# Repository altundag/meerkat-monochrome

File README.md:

# Meerkat Monochrome

Meerkat Monochrome is a monochrome camera project that I started as a hobby. This repository contains the complete design, including PCB layouts, firmware, and supporting tools. The camera hardware consists of:
- an MT9M001C12STM monochrome image sensor
- an RP2354A used as the camera's processing and control unit
- an APS6404L-3SQR QSPI PSRAM for the frame buffer
- an FM25L16B F-RAM to permanently store data (e.g., the frame count)

The image sensor itself is capable of operating at clock speeds up to 48 MHz. However, in this design the pixel clock is set to 6.5 MHz, because the PSRAM frame buffer cannot accept data at higher throughput. This also means the project doesn't require a high-speed PCB, which makes my job easier since I'm not a professional PCB designer.

The PCB design has tiny 0402 components. They require a steady hand, but you can still assemble the board manually using a reflow oven.

The firmware is written entirely in Rust and is actively under development. When this project started, there was no Rust library available to interface with the MT9M001C12STM sensor, so this repository also incleads a tool that automatically generates a library from a JSON sensor description file. Please see the `mt9m001` project for details.

# Examples

An example image taken during prototype PCB testing:

If you have a close look at the image above, you can see the fixed pattern noise. It is more visible when the sensor is evenly exposed to light.

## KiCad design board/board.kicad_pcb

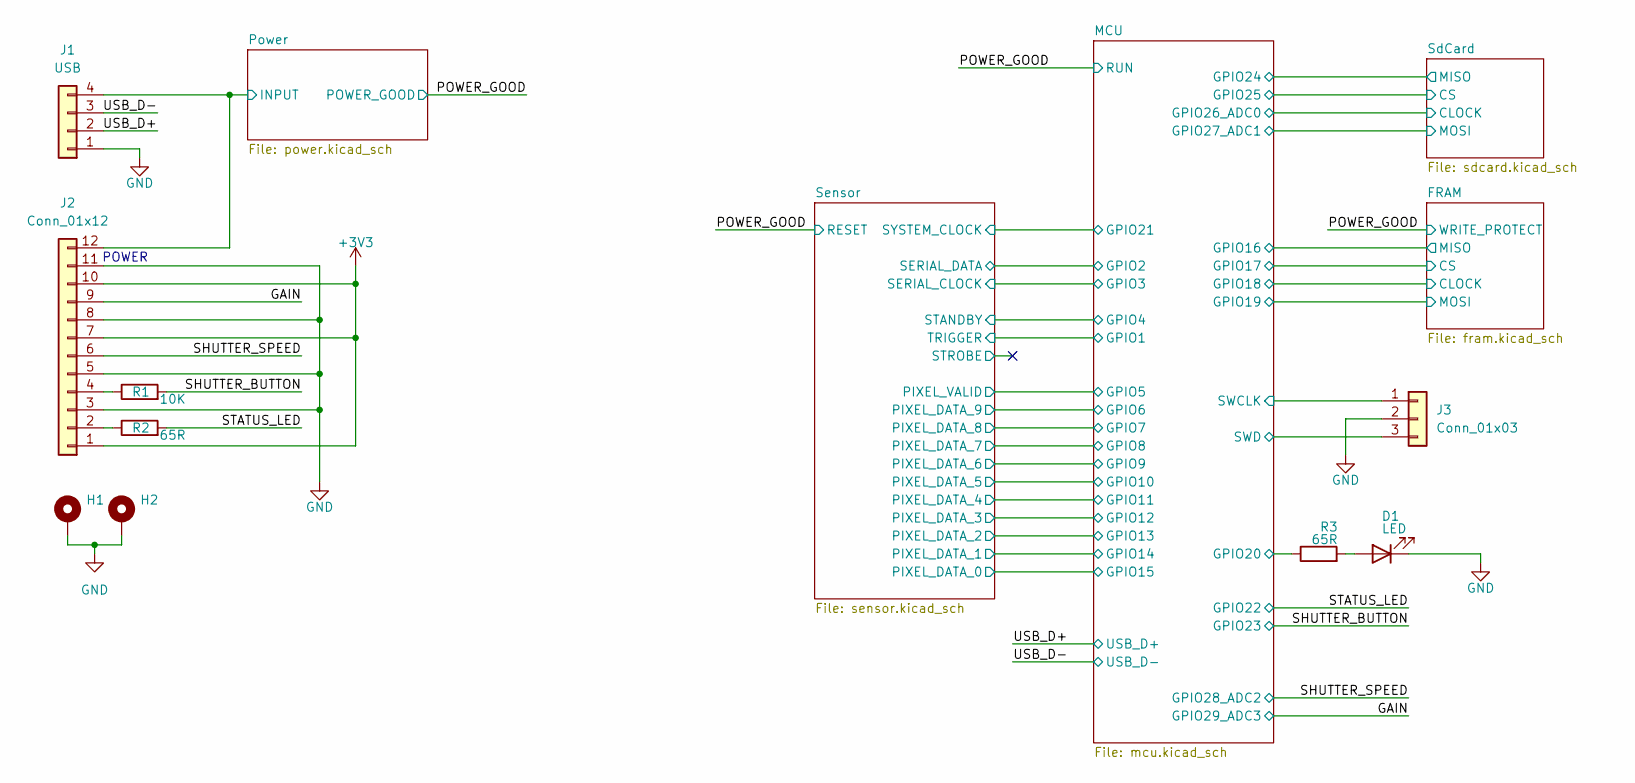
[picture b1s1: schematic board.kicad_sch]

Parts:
D1: LED; LED_0402_1005Metric
H1, H2: MountingHole_Pad; MountingHole_2.2mm_M2_Pad_Via
J1: USB; PinHeader_1x04_P1.27mm_Vertical
J2: Conn_01x12; Hirose_DF52-12S-0.8H_1x12-1MP_P0.80mm_Horizontal
J3: Conn_01x03; PinHeader_1x03_P1.00mm_Vertical
R1: 10K; R_0402_1005Metric
R2, R3: 65R; R_0402_1005Metric

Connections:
+3V3: J2.1, J2.7, J2.10; also elsewhere on the board
/GAIN: J2.9; also elsewhere on the board
/MCU/GPIO20: R3.1; also elsewhere on the board
/MCU/SWCLK: J3.1; also elsewhere on the board
/MCU/SWD: J3.3; also elsewhere on the board
/Power/INPUT: J1.4, J2.12; also elsewhere on the board
/SHUTTER_BUTTON: R1.2; also elsewhere on the board
/SHUTTER_SPEED: J2.6; also elsewhere on the board
/STATUS_LED: R2.2; also elsewhere on the board
/USB_D+: J1.2; also elsewhere on the board
/USB_D-: J1.3; also elsewhere on the board
GND: D1.1 (K), H1.1, H2.1, J1.1, J2.3, J2.5, J2.8, J2.11, J3.2; also elsewhere on the board
unnamed: D1.2 (A), R3.2
unnamed: J2.2, R2.1
unnamed: J2.4, R1.1

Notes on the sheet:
POWER

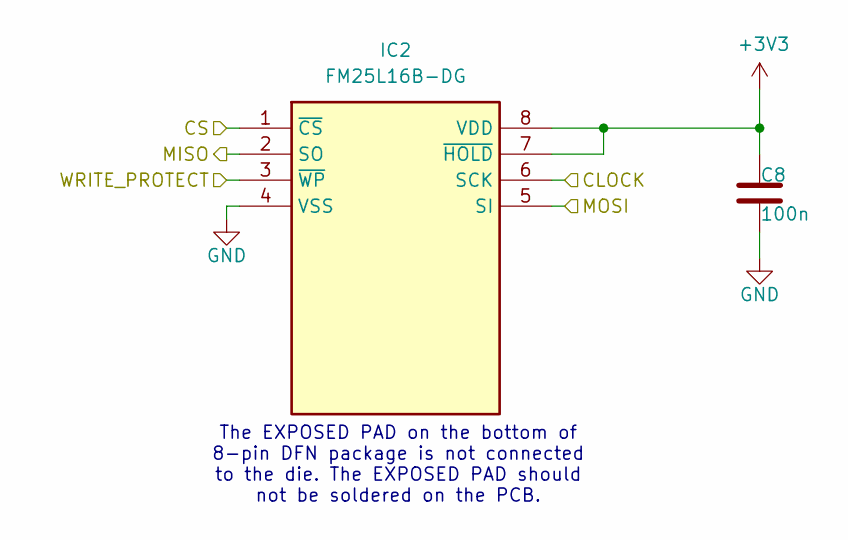
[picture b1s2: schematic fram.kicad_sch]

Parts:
C8: 100n; C_0402_1005Metric
IC2: FM25L16B-DG; Mouser Part Number 877-FM25L16B-DG

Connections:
+3V3: C8.2, IC2.7 (~HOLD), IC2.8 (VDD); also elsewhere on the board
/FRAM/CLOCK: IC2.6 (SCK); also elsewhere on the board
/FRAM/CS: IC2.1 (~CS); also elsewhere on the board
/FRAM/MISO: IC2.2 (SO); also elsewhere on the board
/FRAM/MOSI: IC2.5 (SI); also elsewhere on the board
/POWER_GOOD: IC2.3 (~WP); also elsewhere on the board
GND: C8.1, IC2.4 (VSS); also elsewhere on the board

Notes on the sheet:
The EXPOSED PAD on the bottom of 8-pin DFN package is not connected to the die. The EXPOSED PAD should not be soldered on the PCB.

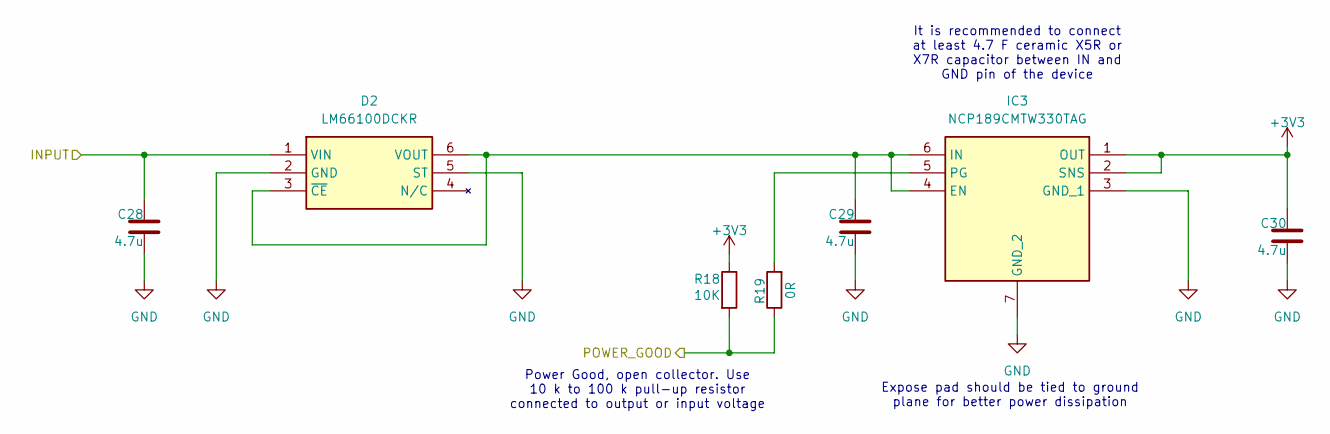
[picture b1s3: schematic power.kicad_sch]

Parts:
C28, C29, C30: 4.7u; C_0402_1005Metric
D2: LM66100DCKR; Mouser Part Number 595-LM66100DCKR
IC3: NCP189CMTW330TAG; Mouser Part Number 863-NCP189CMTW330TAG
R18: 10K; R_0402_1005Metric
R19: 0R; R_0402_1005Metric_small_pads

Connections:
+3V3: C30.2, IC3.1 (OUT), IC3.2 (SNS), R18.1; also elsewhere on the board
/POWER_GOOD: R18.2, R19.1; also elsewhere on the board
/Power/INPUT: C28.2, D2.1 (VIN); also elsewhere on the board
GND: C28.1, C29.1, C30.1, D2.2 (GND), D2.5 (ST), IC3.3 (GND_1), IC3.7 (GND_2); also elsewhere on the board
unnamed: C29.2, D2.3 (~CE), D2.6 (VOUT), IC3.4 (EN), IC3.6 (IN)
unnamed: IC3.5 (PG), R19.2

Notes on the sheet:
Power Good, open collector. Use 10 k to 100 k pull−up resistor connected to output or input voltage
It is recommended to connect at least 4.7 F ceramic X5R or X7R capacitor between IN and GND pin of the device
Expose pad should be tied to ground plane for better power dissipation

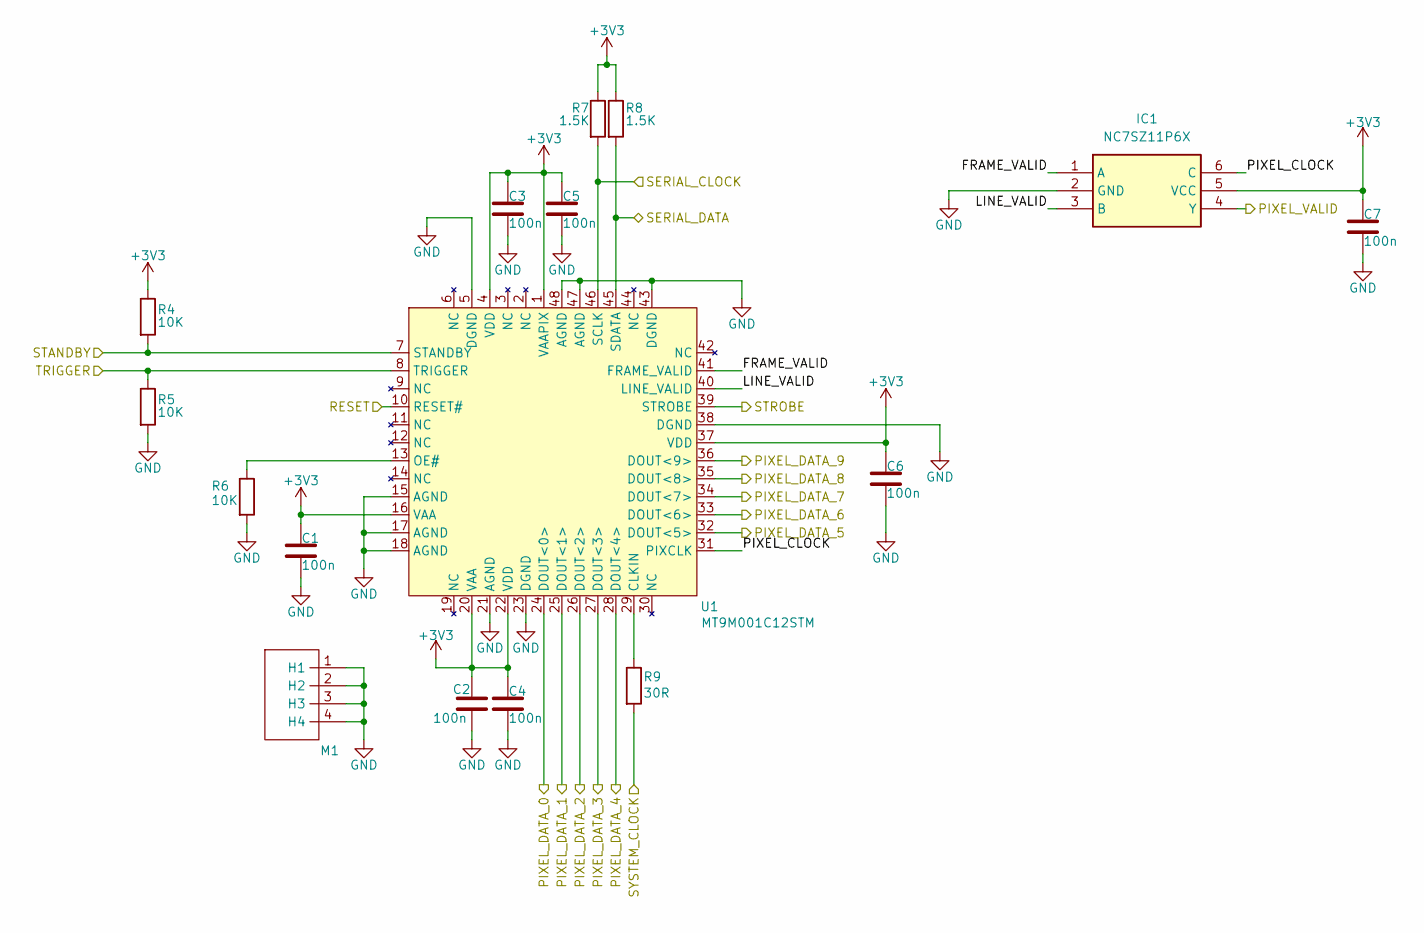
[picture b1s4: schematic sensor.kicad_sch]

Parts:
C1, C2, C3, C4, C5, C6, C7: 100n; C_0402_1005Metric
IC1: NC7SZ11P6X; Mouser Part Number 512-NC7SZ11P6X
M1: c-mount-03
R4, R5, R6: 10K; R_0402_1005Metric
R7, R8: 1.5K; R_0402_1005Metric
R9: 30R; R_0402_1005Metric
U1: MT9M001C12STM

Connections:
+3V3: C1.2, C2.2, C3.2, C4.2, C5.2, C6.2, C7.2, IC1.5 (VCC), R4.1, R7.1, R8.1, U1.1 (VAAPIX), U1.4 (VDD), U1.16 (VAA), U1.20 (VAA), U1.22 (VDD), U1.37 (VDD); also elsewhere on the board
/MCU/GPIO1: R5.1, U1.8 (TRIGGER); also elsewhere on the board
/MCU/GPIO2: R8.2, U1.45 (SDATA); also elsewhere on the board
/MCU/GPIO3: R7.2, U1.46 (SCLK); also elsewhere on the board
/MCU/GPIO4: R4.2, U1.7 (STANDBY); also elsewhere on the board
/MCU/GPIO5: IC1.4 (Y); also elsewhere on the board
/MCU/GPIO6: U1.36 (DOUT<9>); also elsewhere on the board
/MCU/GPIO7: U1.35 (DOUT<8>); also elsewhere on the board
/MCU/GPIO8: U1.34 (DOUT<7>); also elsewhere on the board
/MCU/GPIO9: U1.33 (DOUT<6>); also elsewhere on the board
/MCU/GPIO10: U1.32 (DOUT<5>); also elsewhere on the board
/MCU/GPIO11: U1.28 (DOUT<4>); also elsewhere on the board
/MCU/GPIO12: U1.27 (DOUT<3>); also elsewhere on the board
/MCU/GPIO13: U1.26 (DOUT<2>); also elsewhere on the board
/MCU/GPIO14: U1.25 (DOUT<1>); also elsewhere on the board
/MCU/GPIO15: U1.24 (DOUT<0>); also elsewhere on the board
/MCU/GPIO21: R9.2; also elsewhere on the board
/POWER_GOOD: U1.10 (RESET#); also elsewhere on the board
/Sensor/FRAME_VALID: IC1.1 (A), U1.41 (FRAME_VALID)
/Sensor/LINE_VALID: IC1.3 (B), U1.40 (LINE_VALID)
/Sensor/PIXEL_CLOCK: IC1.6 (C), U1.31 (PIXCLK)
/Sensor/STROBE: U1.39 (STROBE)
GND: C1.1, C2.1, C3.1, C4.1, C5.1, C6.1, C7.1, IC1.2 (GND), M1.1 (H1), M1.2 (H2), M1.3 (H3), M1.4 (H4), R5.2, R6.2, U1.5 (DGND), U1.15 (AGND), U1.17 (AGND), U1.18 (AGND), U1.21 (AGND), U1.23 (DGND), U1.38 (DGND), U1.43 (DGND), U1.47 (AGND), U1.48 (AGND); also elsewhere on the board
unnamed: R9.1, U1.29 (CLKIN)
unnamed: R6.1, U1.13 (OE#)

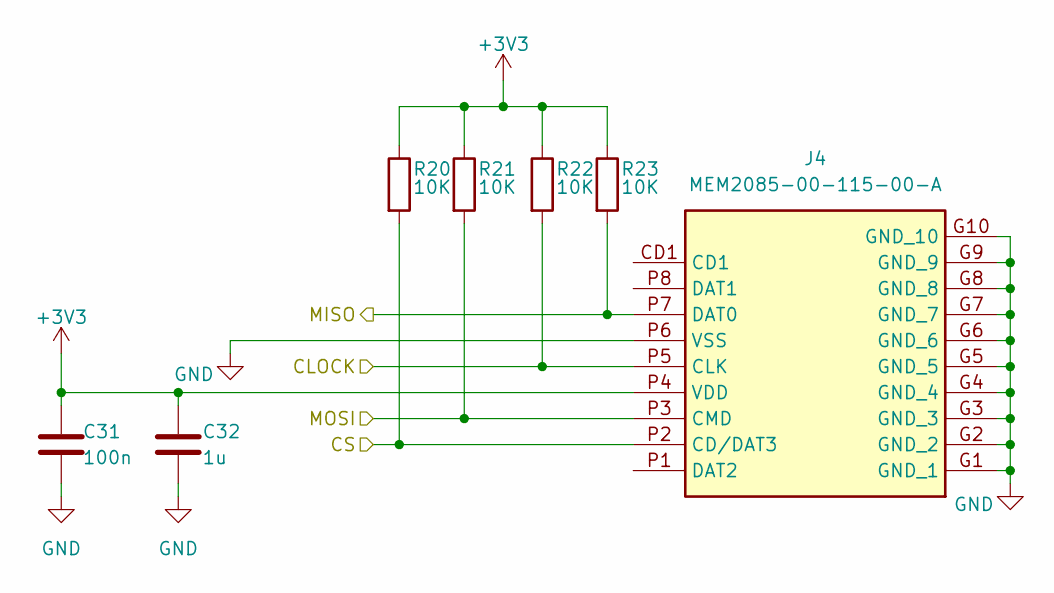
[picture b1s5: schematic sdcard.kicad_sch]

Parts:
C31: 100n; C_0402_1005Metric
C32: 1u; C_0402_1005Metric
J4: MEM2085-00-115-00-A; MEM20850011500A; Mouser Part Number 640-MEM20850011500A
R20, R21, R22, R23: 10K; R_0402_1005Metric_small_pads

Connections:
+3V3: C31.2, C32.2, J4.P4 (VDD), R20.1, R21.1, R22.1, R23.1; also elsewhere on the board
/MCU/GPIO24: J4.P7 (DAT0), R23.2; also elsewhere on the board
/MCU/GPIO25: J4.P2 (CD/DAT3), R20.2; also elsewhere on the board
/MCU/GPIO26_ADC0: J4.P5 (CLK), R22.2; also elsewhere on the board
/MCU/GPIO27_ADC1: J4.P3 (CMD), R21.2; also elsewhere on the board
GND: C31.1, C32.1, J4.G1 (GND_1), J4.G2 (GND_2), J4.G3 (GND_3), J4.G4 (GND_4), J4.G5 (GND_5), J4.G6 (GND_6), J4.G7 (GND_7), J4.G8 (GND_8), J4.G9 (GND_9), J4.G10 (GND_10), J4.P6 (VSS); also elsewhere on the board

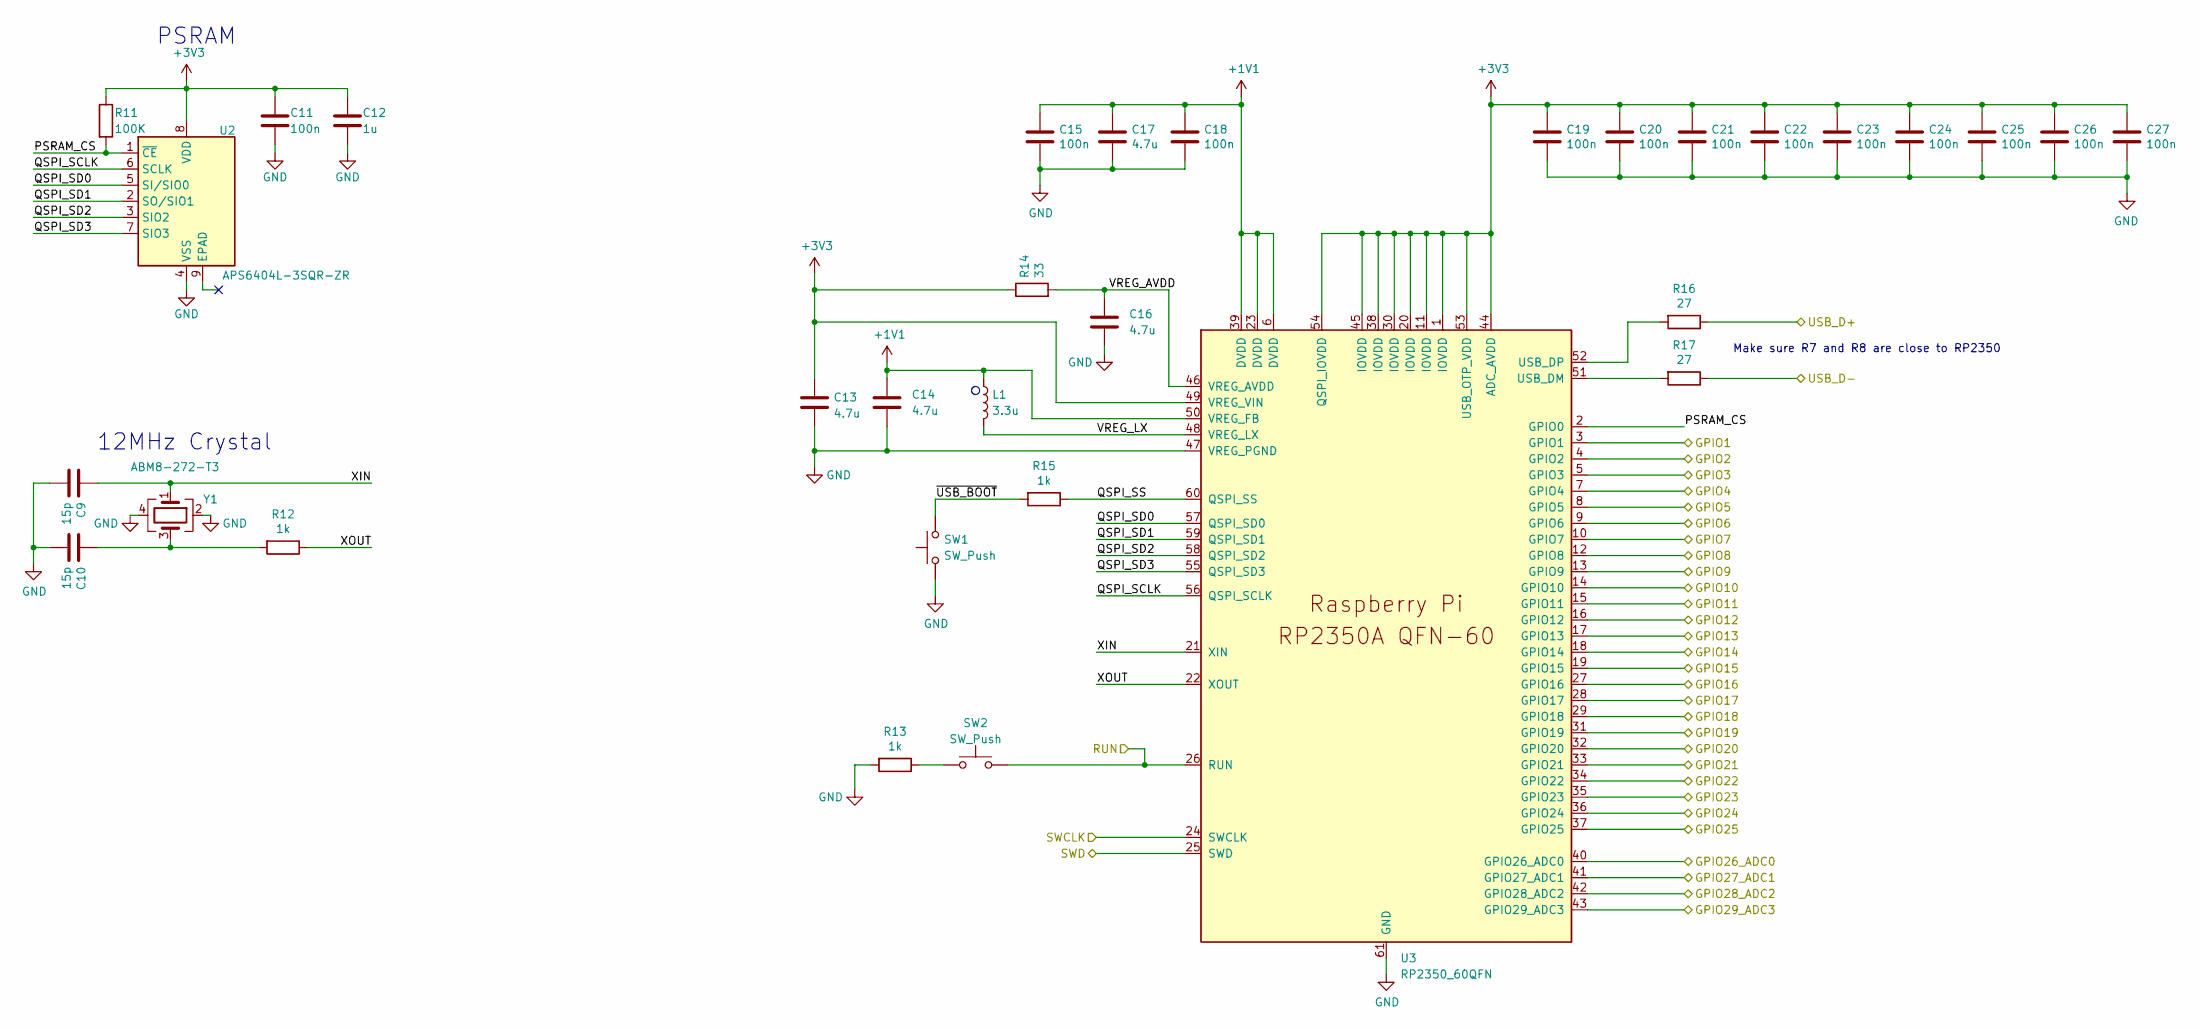
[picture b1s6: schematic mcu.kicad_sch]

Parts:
C9, C10: 15p; C_0402_1005Metric
C11, C15, C18, C19, C20, C21, C22, C23, C24, C25, C26, C27: 100n; C_0402_1005Metric
C12: 1u; C_0402_1005Metric
C13, C14: 4.7u; C_0402_1005Metric_small_pads
C16, C17: 4.7u; C_0402_1005Metric
L1: 3.3u; AOTA-B201610S3R3-101-T
R11: 100K; R_0402_1005Metric_small_pads
R12, R13: 1k; R_0402_1005Metric
R14: 33; R_0402_1005Metric
R15: 1k; R_0402_1005Metric_small_pads
R16, R17: 27; R_0402_1005Metric
SW1, SW2: SW_Push; SW_SPST_B3U-1000P
U2: APS6404L-3SQR-ZR; Winbond_USON-8-1EP_3x2mm_P0.5mm_EP0.2x1.6mm
U3: RP2350_60QFN; RP2350-QFN-60-1EP_7x7_P0.4mm_EP3.4x3.4mm_ThermalVias
Y1: ABM8-272-T3; ABM8272T3

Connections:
+1V1: C14.1, C15.1, C17.1, C18.1, L1.1, U3.6 (DVDD), U3.23 (DVDD), U3.39 (DVDD), U3.50 (VREG_FB)
+3V3: C11.2, C12.2, C13.1, C19.1, C20.1, C21.1, C22.1, C23.1, C24.1, C25.1, C26.1, C27.1, R11.1, R14.1, U2.8 (VDD), U3.1 (IOVDD), U3.11 (IOVDD), U3.20 (IOVDD), U3.30 (IOVDD), U3.38 (IOVDD), U3.44 (ADC_AVDD), U3.45 (IOVDD), U3.49 (VREG_VIN), U3.53 (USB_OTP_VDD), U3.54 (QSPI_IOVDD); also elsewhere on the board
/FRAM/CLOCK: U3.29 (GPIO18); also elsewhere on the board
/FRAM/CS: U3.28 (GPIO17); also elsewhere on the board
/FRAM/MISO: U3.27 (GPIO16); also elsewhere on the board
/FRAM/MOSI: U3.31 (GPIO19); also elsewhere on the board
/GAIN: U3.43 (GPIO29_ADC3); also elsewhere on the board
/MCU/GPIO1: U3.3 (GPIO1); also elsewhere on the board
/MCU/GPIO2: U3.4 (GPIO2); also elsewhere on the board
/MCU/GPIO3: U3.5 (GPIO3); also elsewhere on the board
/MCU/GPIO4: U3.7 (GPIO4); also elsewhere on the board
/MCU/GPIO5: U3.8 (GPIO5); also elsewhere on the board
/MCU/GPIO6: U3.9 (GPIO6); also elsewhere on the board
/MCU/GPIO7: U3.10 (GPIO7); also elsewhere on the board
/MCU/GPIO8: U3.12 (GPIO8); also elsewhere on the board
/MCU/GPIO9: U3.13 (GPIO9); also elsewhere on the board
/MCU/GPIO10: U3.14 (GPIO10); also elsewhere on the board
/MCU/GPIO11: U3.15 (GPIO11); also elsewhere on the board
/MCU/GPIO12: U3.16 (GPIO12); also elsewhere on the board
/MCU/GPIO13: U3.17 (GPIO13); also elsewhere on the board
/MCU/GPIO14: U3.18 (GPIO14); also elsewhere on the board
/MCU/GPIO15: U3.19 (GPIO15); also elsewhere on the board
/MCU/GPIO20: U3.32 (GPIO20); also elsewhere on the board
/MCU/GPIO21: U3.33 (GPIO21); also elsewhere on the board
/MCU/GPIO24: U3.36 (GPIO24); also elsewhere on the board
/MCU/GPIO25: U3.37 (GPIO25); also elsewhere on the board
/MCU/GPIO26_ADC0: U3.40 (GPIO26_ADC0); also elsewhere on the board
/MCU/GPIO27_ADC1: U3.41 (GPIO27_ADC1); also elsewhere on the board
/MCU/PSRAM_CS: R11.2, U2.1 (~CE), U3.2 (GPIO0)
/MCU/QSPI_SCLK: U2.6 (SCLK), U3.56 (QSPI_SCLK)
/MCU/QSPI_SD0: U2.5 (SI/SIO0), U3.57 (QSPI_SD0)
/MCU/QSPI_SD1: U2.2 (SO/SIO1), U3.59 (QSPI_SD1)
/MCU/QSPI_SD2: U2.3 (SIO2), U3.58 (QSPI_SD2)
/MCU/QSPI_SD3: U2.7 (SIO3), U3.55 (QSPI_SD3)
/MCU/QSPI_SS: R15.1, U3.60 (QSPI_SS)
/MCU/SWCLK: U3.24 (SWCLK); also elsewhere on the board
/MCU/SWD: U3.25 (SWD); also elsewhere on the board
/MCU/VREG_AVDD: C16.1, R14.2, U3.46 (VREG_AVDD)
/MCU/VREG_LX: L1.2, U3.48 (VREG_LX)
/MCU/XIN: C9.1, U3.21 (XIN), Y1.1
/MCU/XOUT: R12.1, U3.22 (XOUT)
/MCU/~USB_BOOT: R15.2, SW1.2
/POWER_GOOD: SW2.2, U3.26 (RUN); also elsewhere on the board
/SHUTTER_BUTTON: U3.35 (GPIO23); also elsewhere on the board
/SHUTTER_SPEED: U3.42 (GPIO28_ADC2); also elsewhere on the board
/STATUS_LED: U3.34 (GPIO22); also elsewhere on the board
/USB_D+: R16.1; also elsewhere on the board
/USB_D-: R17.1; also elsewhere on the board
GND: C9.2, C10.2, C11.1, C12.1, C13.2, C14.2, C15.2, C16.2, C17.2, C18.2, C19.2, C20.2, C21.2, C22.2, C23.2, C24.2, C25.2, C26.2, C27.2, R13.2, SW1.1, U2.4 (VSS), U3.47 (VREG_PGND), U3.61 (GND), Y1.2, Y1.4; also elsewhere on the board
unnamed: C10.1, R12.2, Y1.3
unnamed: R13.1, SW2.1
unnamed: R17.2, U3.51 (USB_DM)
unnamed: R16.2, U3.52 (USB_DP)

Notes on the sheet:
Make sure R7 and R8 are close to RP2350
PSRAM
12MHz Crystal

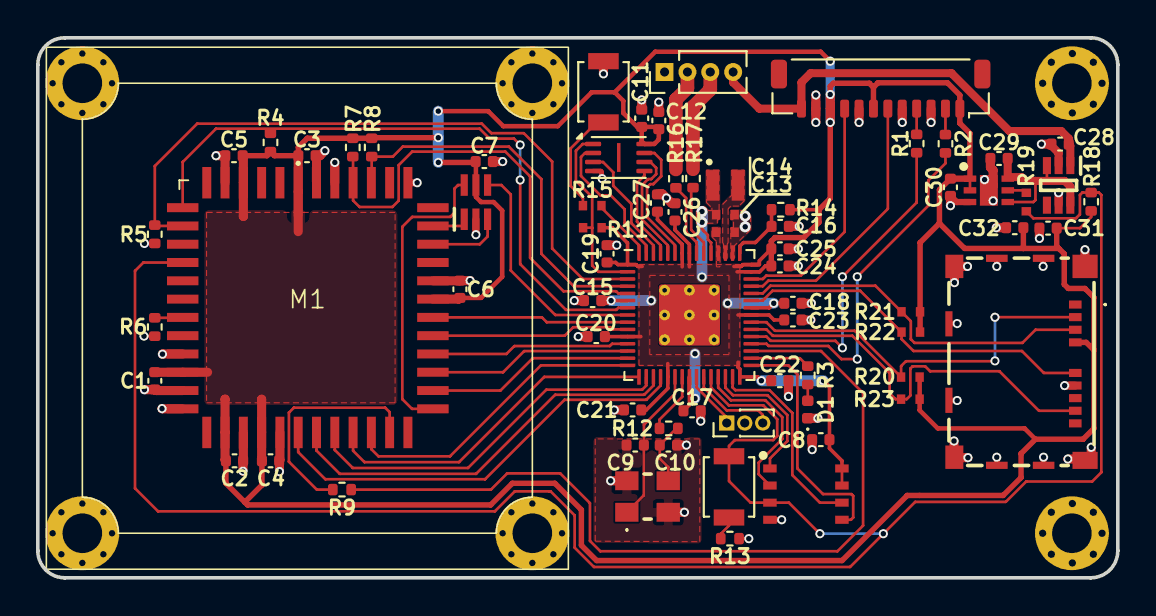
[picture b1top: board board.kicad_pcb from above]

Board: 2 copper layers, 60.0 x 30.0 mm, 73 parts (0 on the bottom side), 64 nets.

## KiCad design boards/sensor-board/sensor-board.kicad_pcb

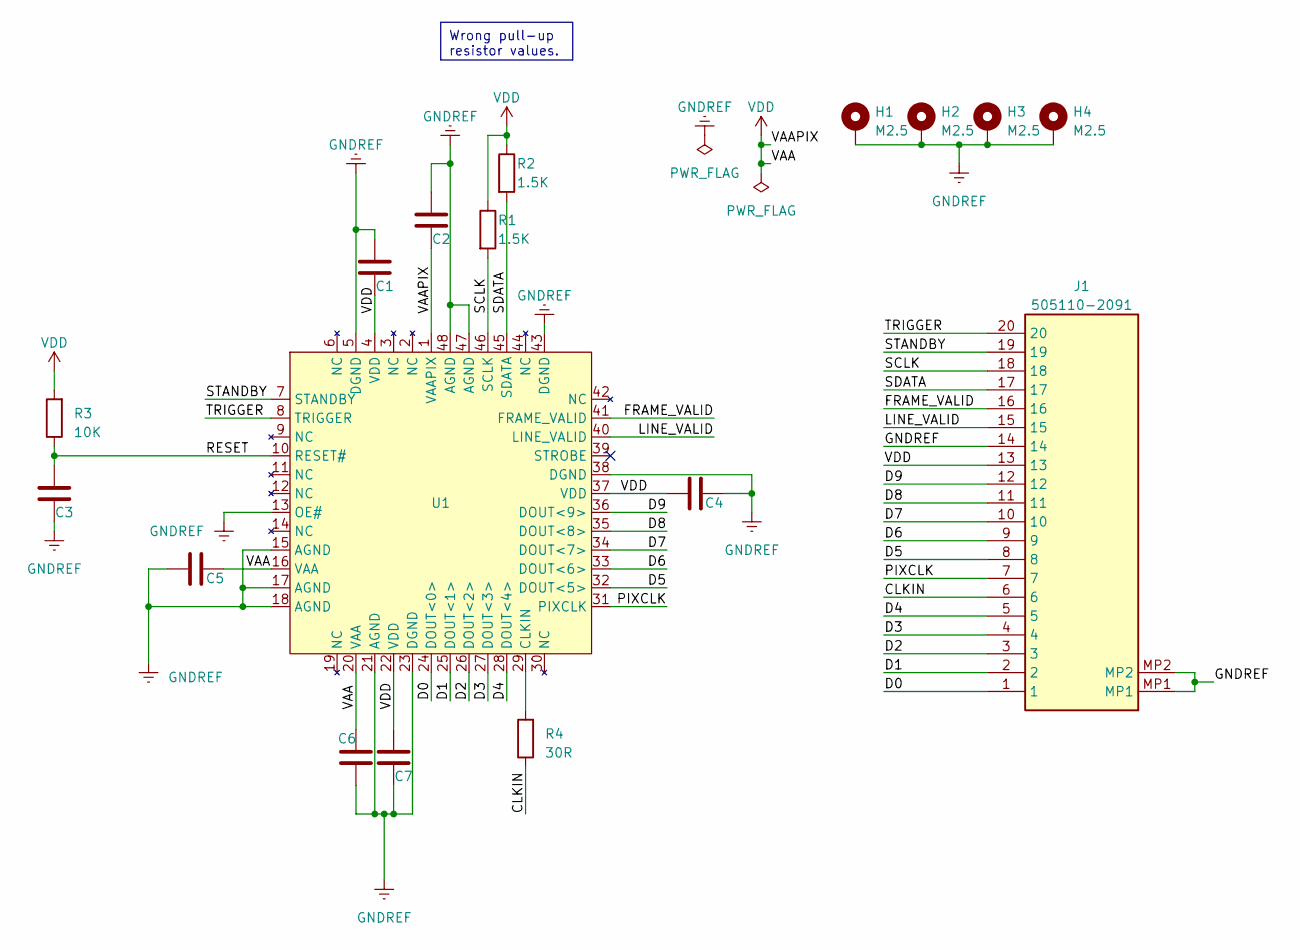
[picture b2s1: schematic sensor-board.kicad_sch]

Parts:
C1, C2, C3, C4, C5, C6, C7: 0.1uF; C_0603_1608Metric
H1, H2, H3, H4: M2.5; MountingHole_2.7mm_M2.5_Pad
J1: 505110-2091; 5051102091; Mouser Part Number 538-505110-2091
R1, R2: 1.5K; R_0603_1608Metric
R3: 10K; R_0603_1608Metric
R4: 30R; R_0603_1608Metric
U1: mt9m001c12stm

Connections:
/CLKIN: J1.6, R4.1
/D0: J1.1, U1.24 (DOUT<0>)
/D1: J1.2, U1.25 (DOUT<1>)
/D2: J1.3, U1.26 (DOUT<2>)
/D3: J1.4, U1.27 (DOUT<3>)
/D4: J1.5, U1.28 (DOUT<4>)
/D5: J1.8, U1.32 (DOUT<5>)
/D6: J1.9, U1.33 (DOUT<6>)
/D7: J1.10, U1.34 (DOUT<7>)
/D8: J1.11, U1.35 (DOUT<8>)
/D9: J1.12, U1.36 (DOUT<9>)
/FRAME_VALID: J1.16, U1.41 (FRAME_VALID)
/LINE_VALID: J1.15, U1.40 (LINE_VALID)
/PIXCLK: J1.7, U1.31 (PIXCLK)
/RESET: C3.2, R3.1, U1.10 (RESET#)
/SCLK: J1.18, R1.2, U1.46 (SCLK)
/SDATA: J1.17, R2.2, U1.45 (SDATA)
/STANDBY: J1.19, U1.7 (STANDBY)
/TRIGGER: J1.20, U1.8 (TRIGGER)
GNDREF: C1.1, C2.1, C3.1, C4.2, C5.1, C6.1, C7.1, H1.1, H2.1, H3.1, H4.1, J1.14, J1.MP1, J1.MP2, U1.5 (DGND), U1.13 (OE#), U1.15 (AGND), U1.17 (AGND), U1.18 (AGND), U1.21 (AGND), U1.23 (DGND), U1.38 (DGND), U1.43 (DGND), U1.47 (AGND), U1.48 (AGND)
unnamed: R4.2, U1.29 (CLKIN)
VDD: C1.2, C2.2, C4.1, C5.2, C6.2, C7.2, J1.13, R1.1, R2.1, R3.2, U1.1 (VAAPIX), U1.4 (VDD), U1.16 (VAA), U1.20 (VAA), U1.22 (VDD), U1.37 (VDD)

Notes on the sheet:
Wrong pull-up resistor values.

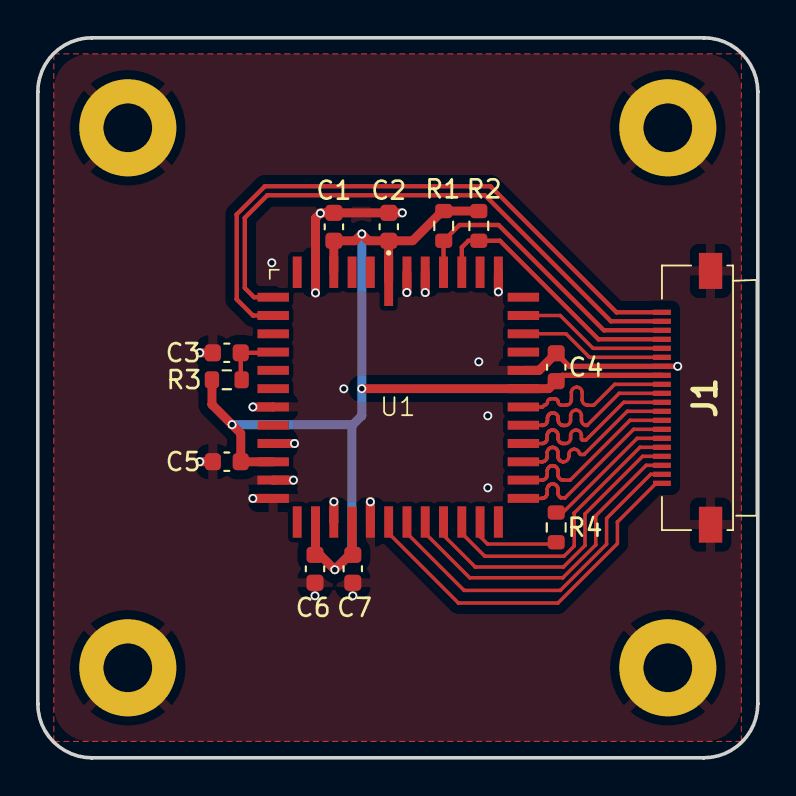
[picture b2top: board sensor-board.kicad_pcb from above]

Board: 2 copper layers, 40.0 x 40.0 mm, 17 parts (0 on the bottom side), 22 nets.

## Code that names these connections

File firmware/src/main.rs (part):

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    let sio = hal::Sio::new(p.SIO);
    let pins = gpio::Pins::new(p.IO_BANK0, p.PADS_BANK0, sio.gpio_bank0, &mut p.RESETS);

    let mut status_led = pins.gpio20.into_push_pull_output();

    // PSRAM setup
    // tPU >= 150us...
    timer.delay_us(300);
    let _cs = pins.gpio0.into_function::<gpio::FunctionXipCs1>();
    let (_, kgd, _) = psram::read_id(&p.QMI);
    if kgd != 0x5D {
        blink(&mut timer, &mut status_led, 3);
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        unsafe { core::slice::from_raw_parts_mut(psram::BASE_ADDRESS as *mut u8, 1024 * 1024 * 8) };

    // FRAM
    let mut fram_cs = pins.gpio17.into_push_pull_output();
    fram_cs.set_high();
    let fram_spi_rx = pins.gpio16.into_function::<gpio::FunctionSpi>();
    let fram_spi_sclk = pins.gpio18.into_function::<gpio::FunctionSpi>();
    let fram_spi_tx = pins.gpio19.into_function::<gpio::FunctionSpi>();
    let fram_spi =
        hal::spi::Spi::<_, _, _, 8>::new(p.SPI0, (fram_spi_tx, fram_spi_rx, fram_spi_sclk));
    let fram_spi = fram_spi.init(
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    let mut fram = fram::FM25L16B::new(fram_cs, fram_spi);

    // Sensor
    let sensor_standby = pins.gpio4.into_push_pull_output_in_state(PinState::Low);
    let sensor_trigger = pins.gpio1.into_push_pull_output_in_state(PinState::Low);
    let _sensor_clock = pins.gpio21.into_function::<gpio::FunctionClock>();
    clocks
        .gpio_output0_clock
        .configure_clock(&clocks.system_clock, sensor::FREQUENCY.Hz())
        .unwrap();
    clocks.gpio_output0_clock.enable();
    let sensor_i2c_sda: gpio::Pin<_, FunctionI2C, _> = pins.gpio2.reconfigure();
    let sensor_i2c_scl: gpio::Pin<_, FunctionI2C, _> = pins.gpio3.reconfigure();
    let sensor_i2c = hal::I2C::i2c1(
        p.I2C1,
        sensor_i2c_sda,
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    );
    let (mut pio, sm0, _, _, _) = p.PIO0.split(&mut p.RESETS);
    let installed_program = pio.install(&pio_capture.program).unwrap();
    let sensor_d0: gpio::Pin<_, gpio::FunctionPio0, _> = pins.gpio6.into_function();
    let sensor_d1: gpio::Pin<_, gpio::FunctionPio0, _> = pins.gpio7.into_function();
    let sensor_d2: gpio::Pin<_, gpio::FunctionPio0, _> = pins.gpio8.into_function();
    let sensor_d3: gpio::Pin<_, gpio::FunctionPio0, _> = pins.gpio9.into_function();
    let sensor_d4: gpio::Pin<_, gpio::FunctionPio0, _> = pins.gpio10.into_function();
    let sensor_d5: gpio::Pin<_, gpio::FunctionPio0, _> = pins.gpio11.into_function();
    let sensor_d6: gpio::Pin<_, gpio::FunctionPio0, _> = pins.gpio12.into_function();
    let sensor_d7: gpio::Pin<_, gpio::FunctionPio0, _> = pins.gpio13.into_function();
    let sensor_d8: gpio::Pin<_, gpio::FunctionPio0, _> = pins.gpio14.into_function();
    let sensor_d9: gpio::Pin<_, gpio::FunctionPio0, _> = pins.gpio15.into_function();
    let sensor_pixel_valid: gpio::Pin<_, gpio::FunctionPio0, _> = pins.gpio5.into_function();
    let (mut sm, rx, _) = hal::pio::PIOBuilder::from_installed_program(installed_program)
        .in_pin_base(sensor_d0.id().num)
        .in_count(10)
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    let mut transfer = single_buffer::Config::new(dma.ch1, rx, image_buf);

    // SDMMC and file system setup
    let sdmmc_spi_rx = pins.gpio24.into_function::<hal::gpio::FunctionSpi>();
    let sdmmc_spi_cs = pins.gpio25.into_push_pull_output();
    let sdmmc_spi_sclk = pins.gpio26.into_function::<hal::gpio::FunctionSpi>();
    let sdmmc_spi_tx = pins.gpio27.into_function::<hal::gpio::FunctionSpi>();
    let sdmmc_spi_bus =
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
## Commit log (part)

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2023-05-03 add zip files
2023-05-03 add fit files
2023-05-24 Minor error type improvements for debugging
2023-05-31 Add new docs
2023-05-31 minor changes
2025-05-04 Initial commit (WIP)
2025-05-30 Add sensor catalog and MT9M034I12STM datasheet
2026-01-03 use embassy
2026-01-11 use embassy, implement minor script improvements, and make minor pcb improvements
2026-02-22 minor improvewments
2026-02-28 switch back to rp235x-hal from embassy
2026-02-28 fix sensor frequency bug and improve README.md
2026-03-13 implement bitpacking
2026-03-13 indicate sensor to psram transfer
2026-04-12 implement tiff support (experimental)
2026-04-12 remove tools/converter.py
2026-04-12 kicad 10.0
2026-04-12 add lm66100 datasheet
2026-04-13 remove unnecessary instructions
2026-04-14 improve tiff implementation and fix pio program name bug
2026-04-28 rm dimensions.txt
